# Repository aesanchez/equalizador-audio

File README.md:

# Ecualizador de audio de 4 bandas

Proyecto de procesamiento digital mediante la placa de desarrollo de la EDU-CIAA, con el fin de implementar un ecualizador de audio de 4 bandas mediante circuitos de acondicionamiento de señales y filtros digitales FIR.

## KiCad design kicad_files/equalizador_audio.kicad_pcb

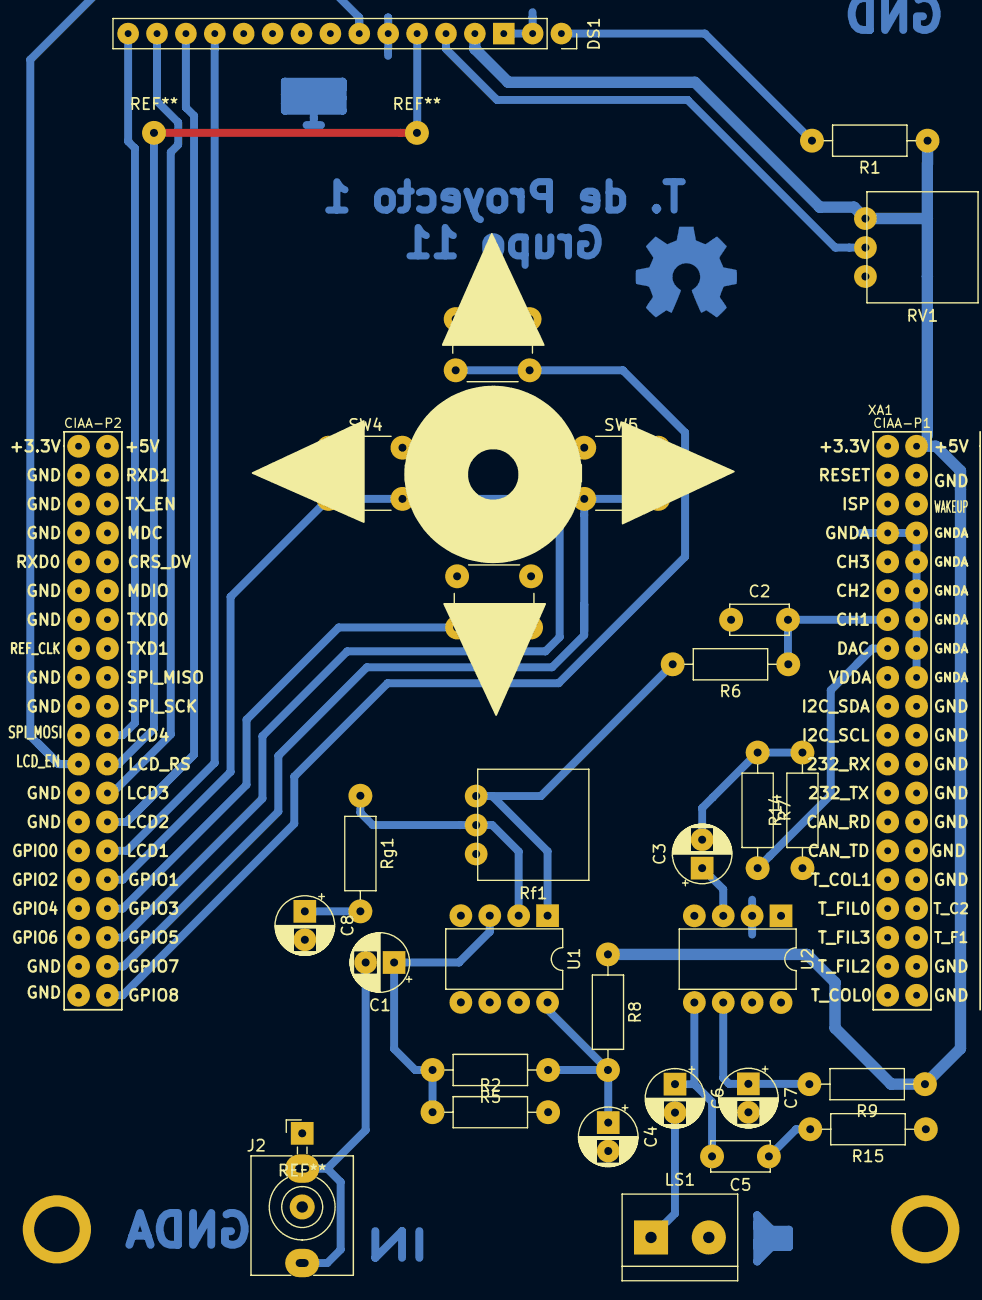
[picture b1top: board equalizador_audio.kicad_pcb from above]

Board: 2 copper layers, 31 parts (0 on the bottom side), 32 nets.

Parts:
C1, C3, C4, C7: 10uF; CP_Radial_D5.0mm_P2.50mm
C2: 0.01uF; C_Disc_D5.0mm_W2.5mm_P5.00mm
C5: 47nF; C_Disc_D5.0mm_W2.5mm_P5.00mm
C6: 250Uf; CP_Radial_D5.0mm_P2.50mm
C8: 1F; CP_Radial_D5.0mm_P2.50mm
DS1: LCD16X2; LCD-Catedra
J2: Audio_JACK_2P; Jack_3.5mm_QingPu_WQP-PJ398SM_Vertical_CircularHoles
LS1: 8 Ohm; TerminalBlock_bornier-2_P5.08mm
R1, R8, R9: 100; R_Axial_DIN0207_L6.3mm_D2.5mm_P10.16mm_Horizontal
R2: 100k; R_Axial_DIN0207_L6.3mm_D2.5mm_P10.16mm_Horizontal
R5: 220k; R_Axial_DIN0207_L6.3mm_D2.5mm_P10.16mm_Horizontal
R6: ~636; R_Axial_DIN0207_L6.3mm_D2.5mm_P10.16mm_Horizontal
R7: 30k; R_Axial_DIN0207_L6.3mm_D2.5mm_P10.16mm_Horizontal
R14: 1k; R_Axial_DIN0207_L6.3mm_D2.5mm_P10.16mm_Horizontal
R15: 10; R_Axial_DIN0207_L6.3mm_D2.5mm_P10.16mm_Horizontal
RV1: 10K; potenciometro_acostado
Rf1: 10K; potenciometro_acostado
Rg1: 10k; R_Axial_DIN0207_L6.3mm_D2.5mm_P10.16mm_Horizontal
SW1, SW2, SW3, SW4, SW5: SW_Push; SW_PUSH_6mm_H5mm
U1: LM358; DIP-8_W7.62mm
U2: LM386; DIP-8_W7.62mm
XA1: Conn_Poncho2P_2x_20x2; poncho_recortado

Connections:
+3V3: XA1.1, XA1.41
+5V: DS1.2, R1.1, R8.1, R9.1, RV1.1, XA1.2, XA1.42
/Audio_IN/ADC: C2.2, R6.1, XA1.13
/Audio_IN/Vcca_desacoplada: C4.1, R5.1, R8.2, U1.8
/Audio_OUT/DAC: R7.2, XA1.15
/EDU-CIAA-P2/LCD1: DS1.11, XA1.70
/EDU-CIAA-P2/LCD2: DS1.12, XA1.68
/EDU-CIAA-P2/LCD3: DS1.13, XA1.66
/EDU-CIAA-P2/LCD4: DS1.14, XA1.62
/EDU-CIAA-P2/LCD_EN: DS1.6, XA1.63
/EDU-CIAA-P2/RS: DS1.4, XA1.64
/EDU-CIAA-P2/TEC_DOWN: SW2.2, XA1.74
/EDU-CIAA-P2/TEC_LEFT: SW4.2, XA1.72
/EDU-CIAA-P2/TEC_OK: SW3.2, XA1.76
/EDU-CIAA-P2/TEC_RIGHT: SW5.2, XA1.78
/EDU-CIAA-P2/TEC_UP: SW1.2, XA1.80
GND: DS1.1, DS1.5, DS1.7, DS1.8, DS1.9, DS1.10, DS1.16, RV1.3, SW1.1, SW2.1, SW3.1, SW4.1, SW5.1, XA1.20, XA1.22, XA1.24, XA1.26, XA1.28, XA1.30, XA1.32, XA1.43, XA1.45, XA1.47, XA1.51, XA1.53, XA1.57, XA1.59, XA1.65, XA1.67, XA1.77, XA1.79
GNDA: C2.1, C4.2, C7.2, C8.2, J2.1, LS1.2, R2.2, R14.1, R15.1, U1.4, U2.2, U2.4, XA1.7, XA1.8, XA1.10, XA1.12, XA1.14, XA1.16, XA1.18
unnamed: C1.1, R2.1, R5.2, U1.3
unnamed: C1.2, J2.2, J2.3
unnamed: C3.1, U2.3
unnamed: C3.2, R7.1, R14.2
unnamed: C5.1, R15.2
unnamed: C5.2, C6.1, U2.5
unnamed: C6.2, LS1.1
unnamed: C7.1, R9.2, U2.6
unnamed: C8.1, Rg1.2
unnamed: DS1.3, RV1.2
unnamed: DS1.15, R1.2
unnamed: R6.2, Rf1.1, U1.1
unnamed: Rf1.2, Rg1.1, U1.2
unnamed: XA1.38, XA1.40

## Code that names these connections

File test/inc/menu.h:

#ifndef _MENU_H_
#define _MENU_H_

#ifdef __cplusplus
extern "C" {
#endif

#define TEC_UP GPIO8
#define TEC_RIGHT GPIO7
#define TEC_OK GPIO5
#define TEC_DOWN GPIO3
#define TEC_LEFT GPIO1

void menu_init(void);
void menu_loop(void);
float menu_get_level(void);

#ifdef __cplusplus
}
#endif

#endif 

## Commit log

2018-09-11 init
2018-09-11 readme
2018-09-17 fixes
2018-09-24 esquematico placa perforada
2018-09-24 Implementacion LCD
2018-09-26 Pantalla andando
2018-09-27 andando accurate
2018-09-27 no hace falta
2019-02-27 secciones del projecto final
2019-02-27 Se usan funciones assembler para disminuir tiempos de calculo
2019-02-28 equalizador integrado andando a medias
2019-02-28 anda! falta formatear codigo
2019-02-28 refactoreo
2019-03-01 ui refactor
2019-03-01 refactor para el proyecto
2019-03-02 informe final
2019-03-27 correciones
2019-03-27 refactor y kicad files
